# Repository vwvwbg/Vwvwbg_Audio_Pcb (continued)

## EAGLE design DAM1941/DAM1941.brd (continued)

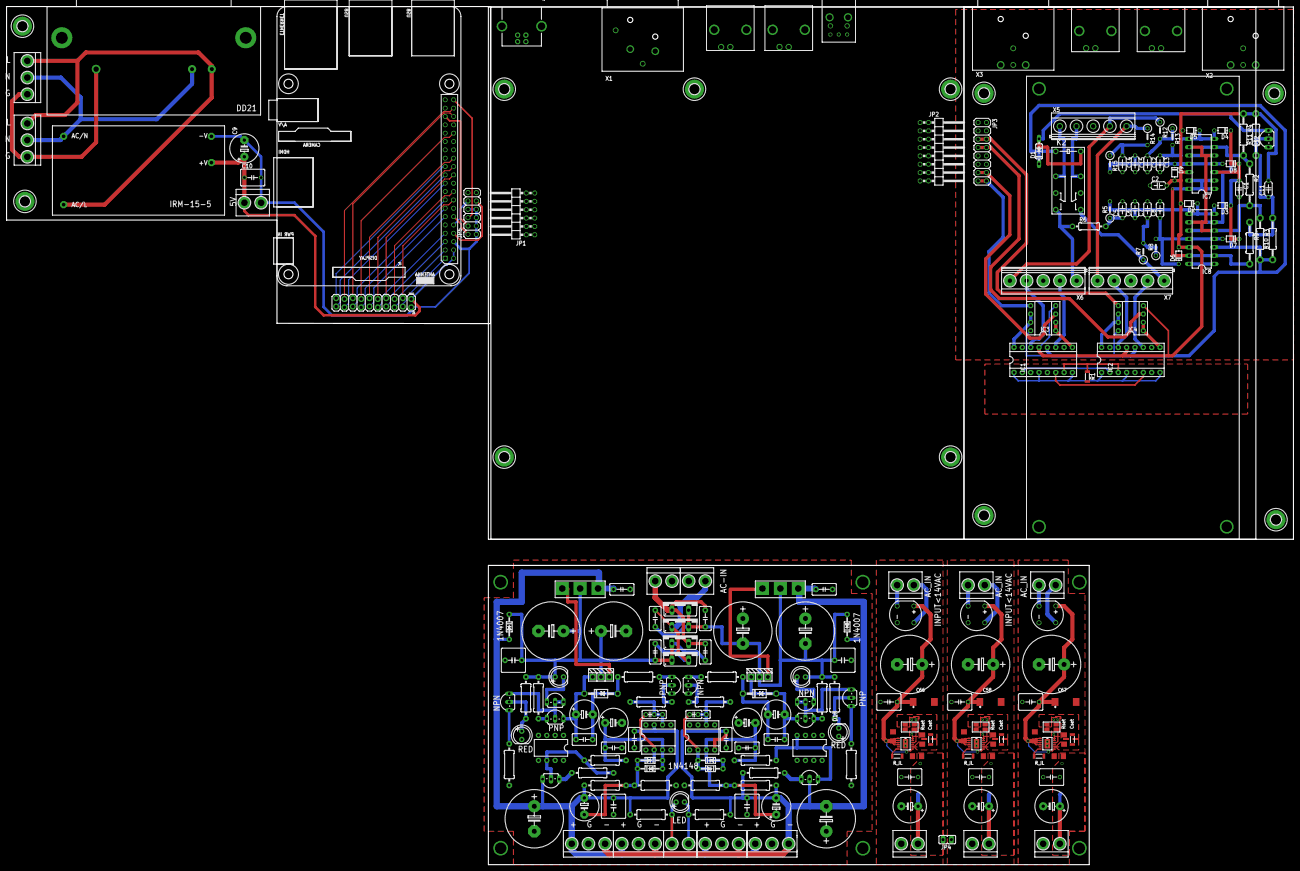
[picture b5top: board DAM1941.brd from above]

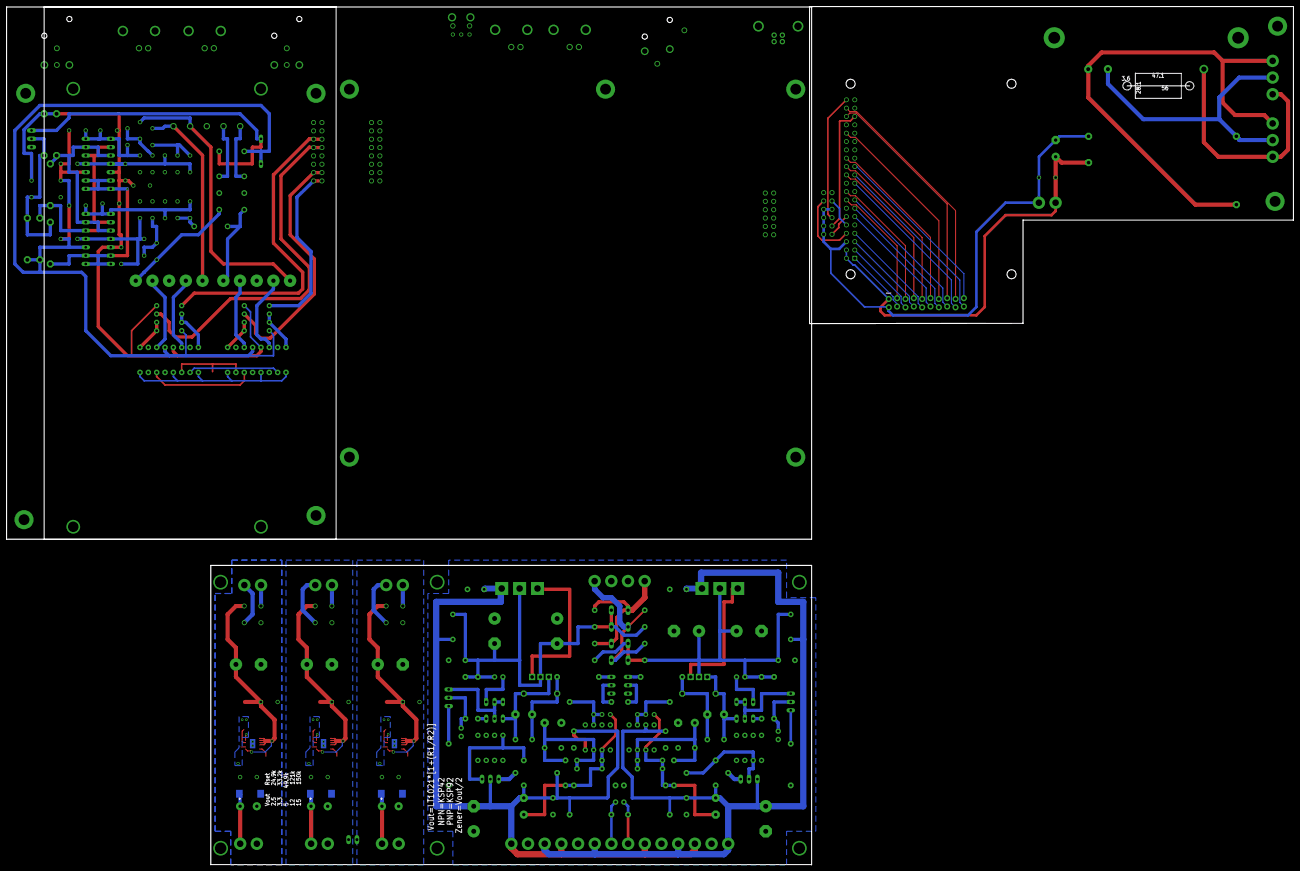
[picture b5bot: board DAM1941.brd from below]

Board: 2 copper layers, 391.8 x 261.2 mm, 221 parts (4 on the bottom side), 133 nets.

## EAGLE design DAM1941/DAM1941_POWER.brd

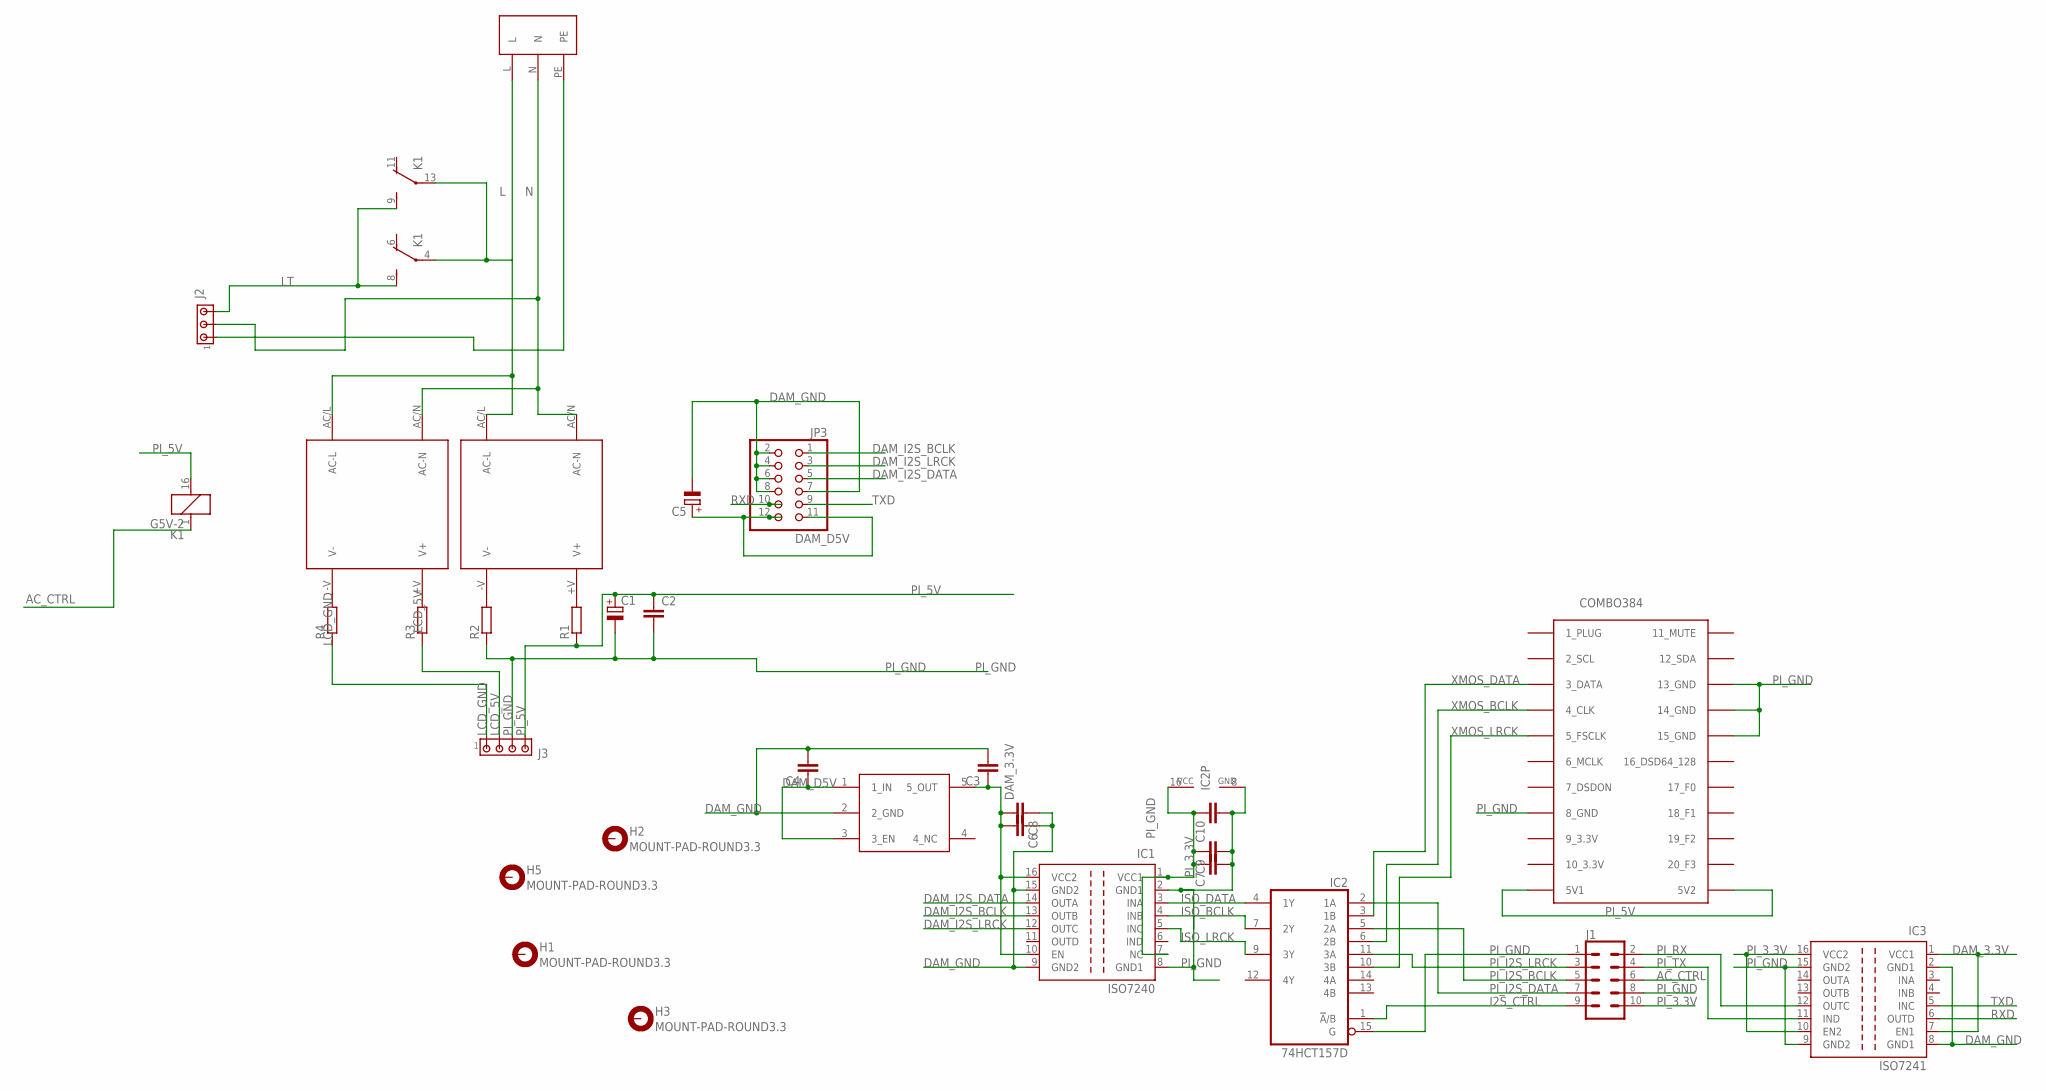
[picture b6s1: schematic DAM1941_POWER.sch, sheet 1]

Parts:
C1: CPOL-EUE5-8.5; E5-8,5
C2: C-EU050-050X075; C050-050X075
C3, C4, C6, C7, C8, C9, C10: C-EUC0805; C0805
C5: CPOL-EUSP-CAP-CX; SP-CAP-CX
H1, H2, H3, H5: MOUNT-PAD-ROUND3.3; 3,3-PAD
IC1: ISO7240; SO-16DW
IC2: 74HCT157D; SO16
IC3: ISO7241; SO-16DW
J1: CONN_05X2SHD_LOCK; 2X5-SHROUDED_LOCK
J2: MTA03-156; 1X3MTA
J3: MTA04-156; 1X4MTA
JP3: PINHD-2X6; 2X06
K1: G5V-2
R1, R2, R3, R4: R-EU_M1206; M1206
U$1: IRM-15-5; IRM-15
U$2: LP5907; SOT-23-5
U$3: IRM-10
U$4: COMBO384+8675
U$6: DD21; DD21.NOCOVER

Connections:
AC_CTRL: J1.6, K1.1
DAM_3.3V: C3.1, C6.2, C8.2, IC1.10 (EN), IC1.16 (VCC2), IC3.1 (VCC1), IC3.7 (EN1), U$2.5 (5_OUT)
DAM_D5V: C4.1, C5.+, JP3.11, JP3.12, U$2.1 (1_IN), U$2.3 (3_EN)
DAM_GND: C3.2, C4.2, C5.-, C6.1, C8.1, IC1.9 (GND2), IC1.15 (GND2), IC3.2 (GND1), IC3.8 (GND1), JP3.2, JP3.4, JP3.6, JP3.7, JP3.8, U$2.2 (2_GND)
DAM_I2S_BCLK: IC1.13 (OUTB), JP3.1
DAM_I2S_DATA: IC1.14 (OUTA), JP3.5
DAM_I2S_LRCK: IC1.12 (OUTC), JP3.3
I2S_CTRL: IC2.1 (!A!/B), J1.9
ISO_BCLK: IC1.4 (INB), IC2.7 (2Y)
ISO_DATA: IC1.3 (INA), IC2.4 (1Y)
ISO_LRCK: IC1.5 (INC), IC2.9 (3Y)
L: K1.4, K1.13, U$1.AC/L (AC-L), U$3.AC/L (AC-L), U$6.L
LCD_5V: J3.2, R3.1
LCD_GND: J3.1, R4.1
LT: J2.3, K1.8 (S), K1.9 (S)
N: J2.2, U$1.AC/N (AC-N), U$3.AC/N (AC-N), U$6.N
unnamed: R1.2, U$1.+V (V+)
unnamed: J2.1, U$6.PE
unnamed: R2.2, U$1.-V (V-)
unnamed: R3.2, U$3.+V (V+)
unnamed: R4.2, U$3.-V (V-)
PI_3.3V: C7.1, C9.1, C10.1, IC1.1 (VCC1), IC1.7 (NC), IC2.16 (VCC), IC3.10 (EN2), IC3.16 (VCC2), J1.10
PI_5V: C1.+, C2.1, J3.4, K1.16 (2), R1.1, U$4.5V1, U$4.5V2
PI_GND: C1.-, C2.2, C7.2, C9.2, C10.2, IC1.2 (GND1), IC1.8 (GND1), IC2.8 (GND), IC2.15 (G), IC3.9 (GND2), IC3.15 (GND2), J1.1, J1.8, J3.3, R2.1, U$4.8_GND, U$4.13_GND, U$4.14_GND, U$4.15_GND
PI_I2S_BCLK: IC2.5 (2A), J1.5
PI_I2S_DATA: IC2.2 (1A), J1.7
PI_I2S_LRCK: IC2.11 (3A), J1.3
PI_RX: IC3.12 (OUTC), J1.2
PI_TX: IC3.11 (IND), J1.4
RXD: IC3.6 (OUTD), JP3.10
TXD: IC3.5 (INC), JP3.9
XMOS_BCLK: IC2.6 (2B), U$4.4_CLD/DSDCLK (4_CLK)
XMOS_DATA: IC2.3 (1B), U$4.3_DATA/DSD1 (3_DATA)
XMOS_LRCK: IC2.10 (3B), U$4.5_FSCLK/DSD2 (5_FSCLK)

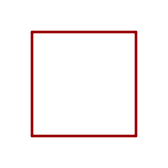
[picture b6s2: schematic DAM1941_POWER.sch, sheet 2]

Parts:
PCB2: RPI3-HOLE

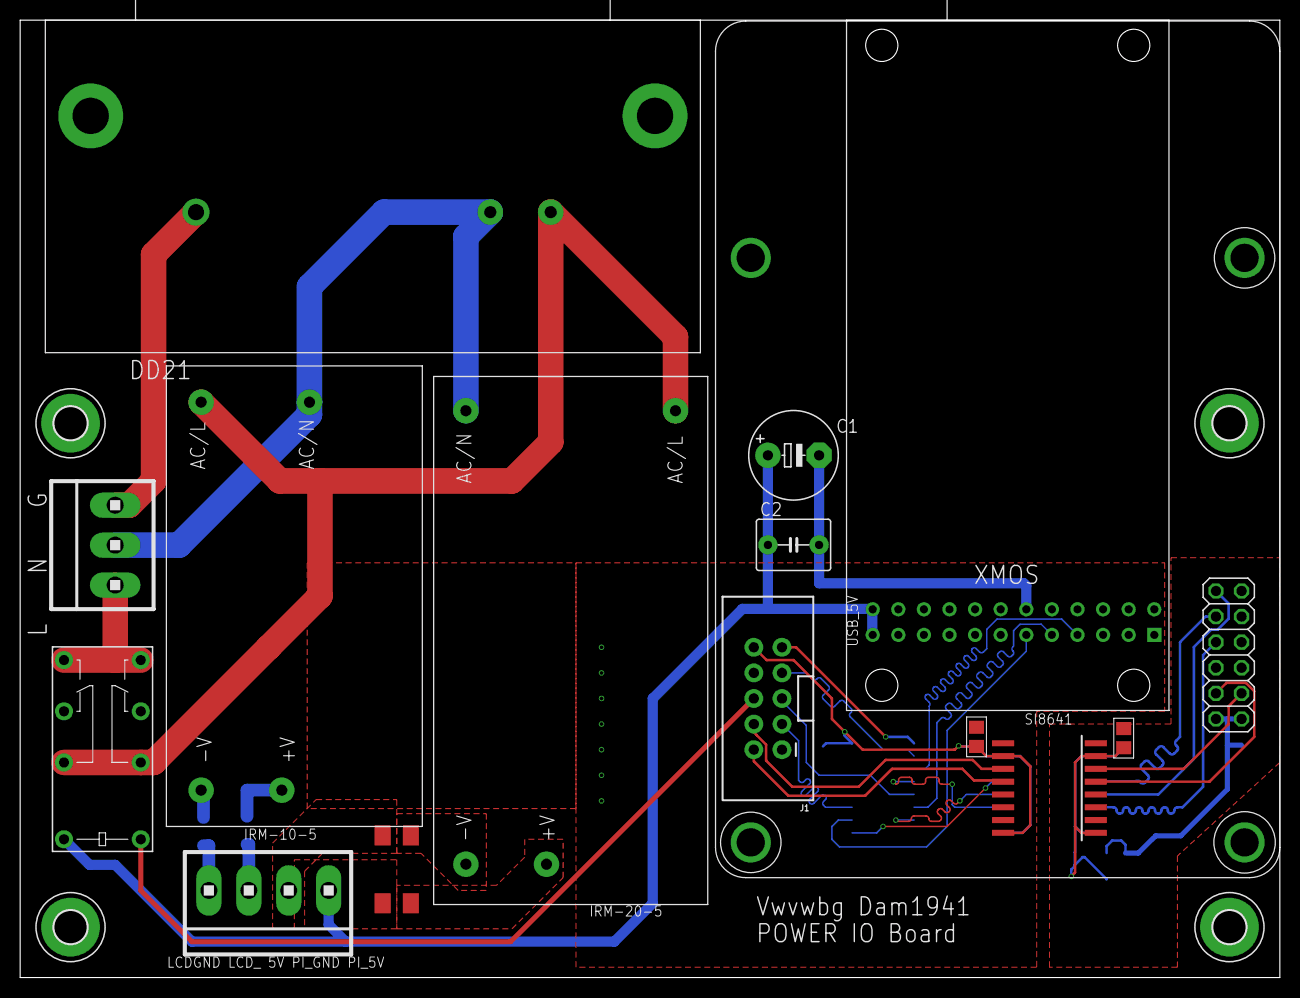
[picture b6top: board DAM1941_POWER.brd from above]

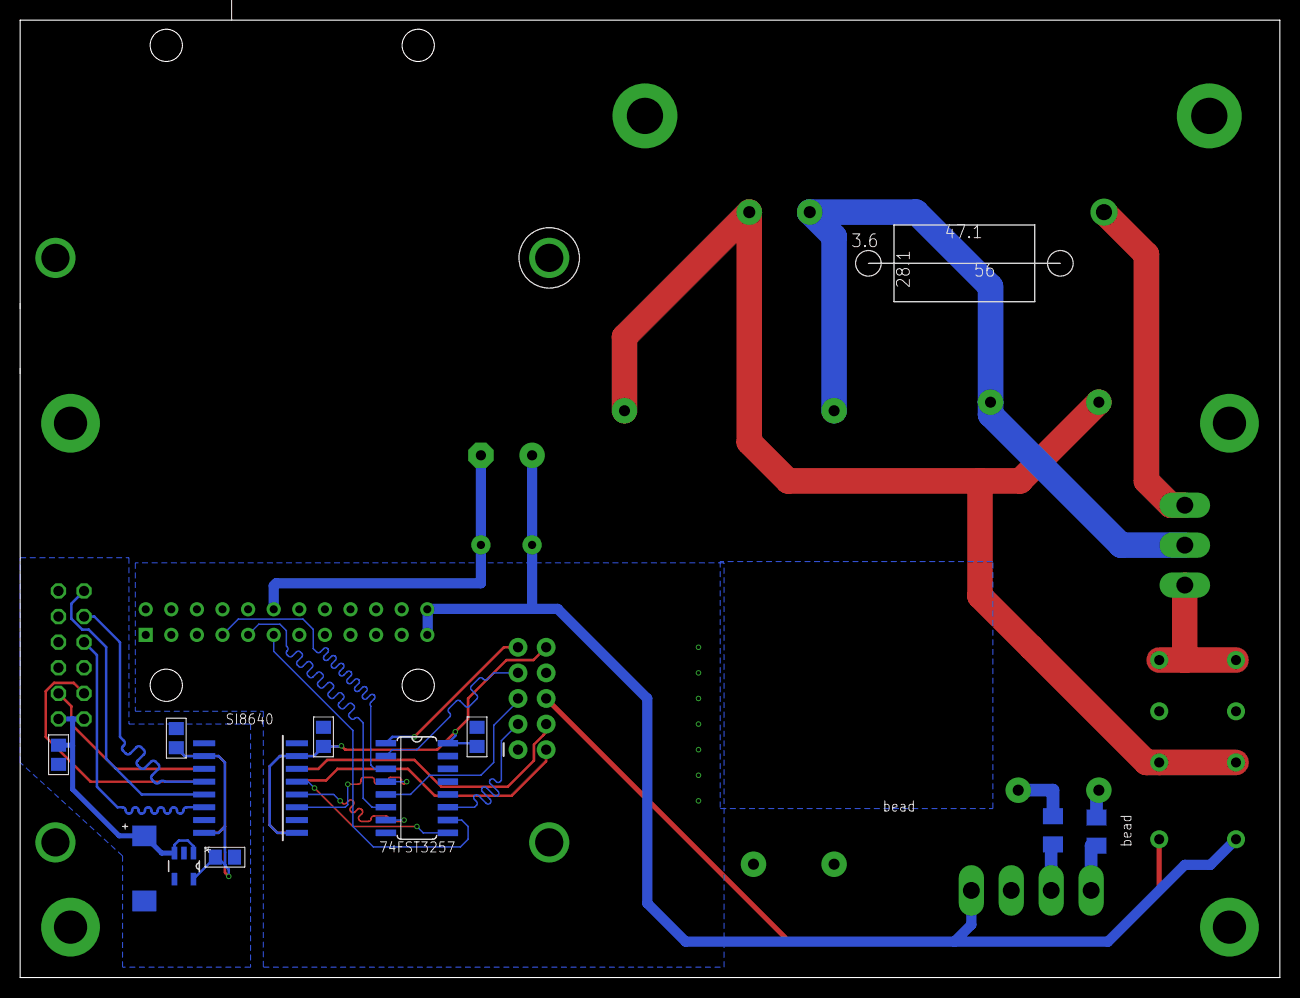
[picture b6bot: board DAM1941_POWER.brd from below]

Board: 2 copper layers, 125.0 x 95.0 mm, 32 parts (12 on the bottom side), 34 nets.

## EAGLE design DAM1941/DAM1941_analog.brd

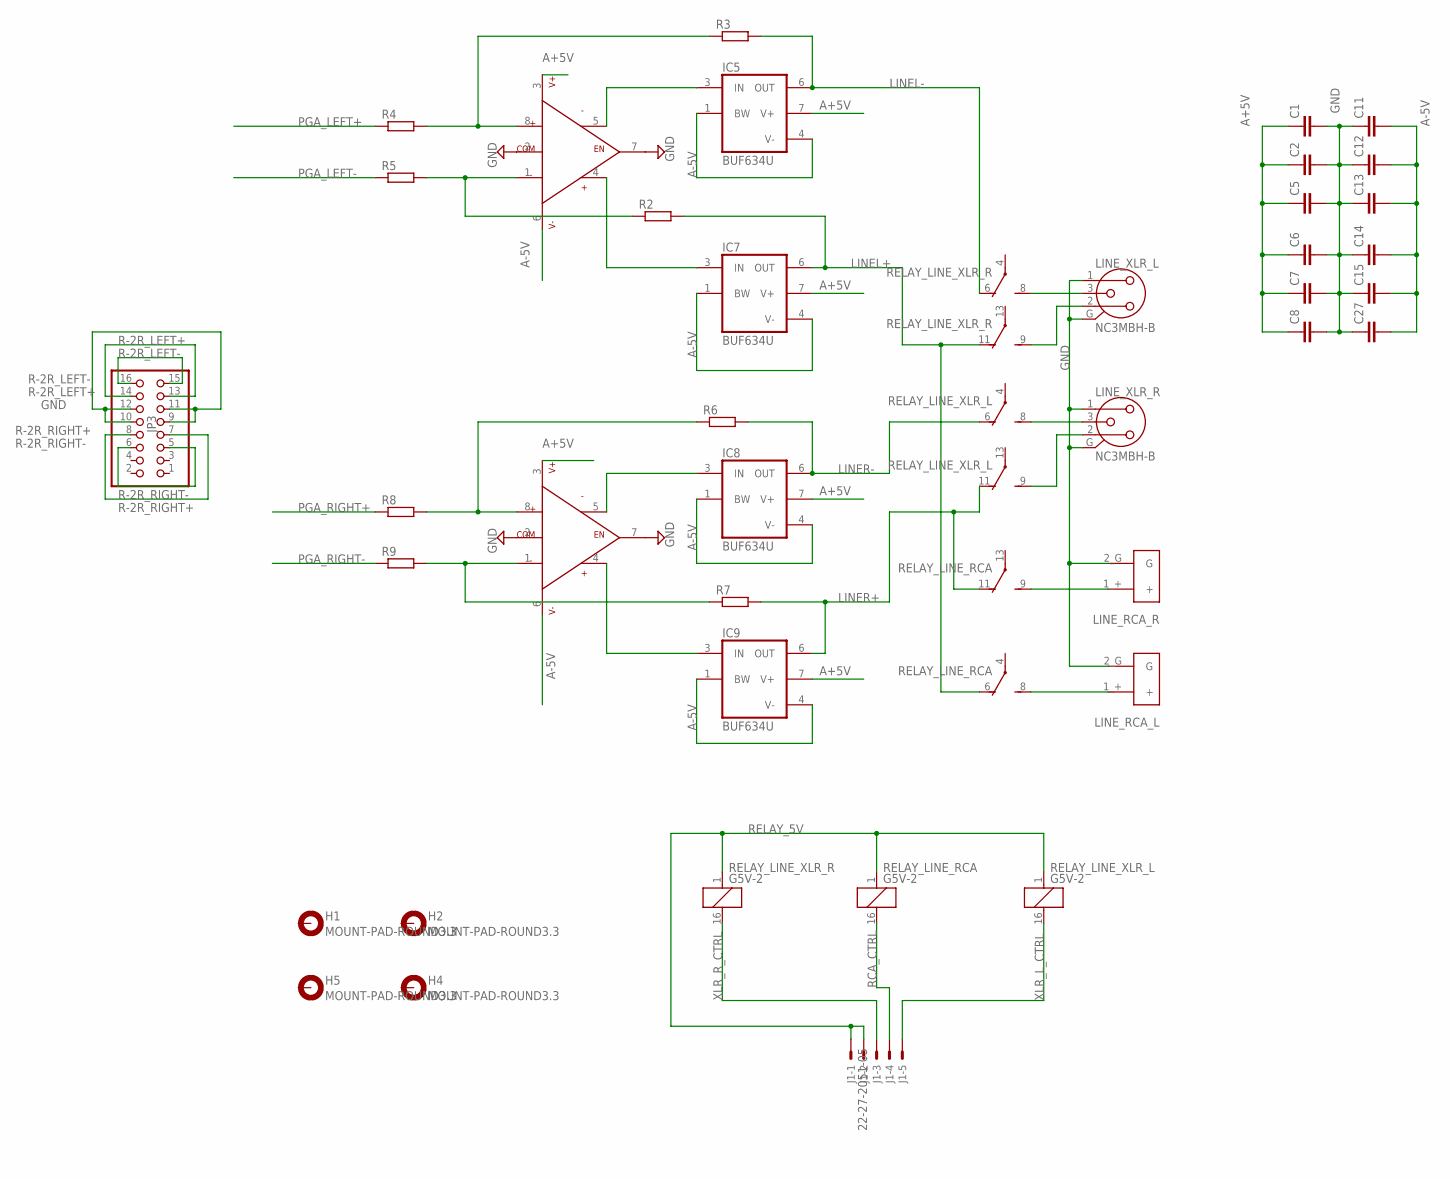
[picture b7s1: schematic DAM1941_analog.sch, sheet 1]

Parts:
C1, C2, C5, C6, C7, C8, C11, C12, C13, C14, C15, C27: C-EU050-050X075; C050-050X075
H1, H2, H4, H5: MOUNT-PAD-ROUND3.3; 3,3-PAD
IC5, IC7, IC8, IC9: BUF634U; SO08
J1: 22-27-2051-05; 6410-05
JP3: PINHD-2X8; 2X08
LINE_RCA_L: RCA
LINE_RCA_R: RCA
LINE_XLR_L: NC3MBH-B
LINE_XLR_R: NC3MBH-B
R2, R3, R4, R5, R6, R7, R8, R9: R-EU_0207/10; 0207/10
RELAY_LINE_RCA: G5V-2
RELAY_LINE_XLR_L: G5V-2
RELAY_LINE_XLR_R: G5V-2
U$1, U$2: OPA1632; SO8

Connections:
A+5V: C1.1, C2.1, C5.1, C6.1, C7.1, C8.1, IC5.7 (V+), IC7.7 (V+), IC8.7 (V+), IC9.7 (V+), U$1.3 (V+), U$2.3 (V+); also elsewhere on the board
A-5V: C11.2, C12.2, C13.2, C14.2, C15.2, C27.2, IC5.1 (BW), IC5.4 (V-), IC7.1 (BW), IC7.4 (V-), IC8.1 (BW), IC8.4 (V-), IC9.1 (BW), IC9.4 (V-), U$1.6 (V-), U$2.6 (V-); also elsewhere on the board
GND: C1.2, C2.2, C5.2, C6.2, C7.2, C8.2, C11.1, C12.1, C13.1, C14.1, C15.1, C27.1, JP3.9, JP3.10, JP3.11, JP3.12, LINE_RCA_L.2_G (G), LINE_RCA_R.2_G (G), LINE_XLR_L.1, LINE_XLR_L.G, LINE_XLR_R.1, LINE_XLR_R.G, U$1.2 (COM), U$1.7 (EN), U$2.2 (COM), U$2.7 (EN); also elsewhere on the board
LINEL+: IC7.6 (OUT), R2.2, RELAY_LINE_RCA.6 (O), RELAY_LINE_XLR_R.11 (O)
LINEL-: IC5.6 (OUT), R3.2, RELAY_LINE_XLR_R.6 (O)
LINER+: IC9.6 (OUT), R7.2, RELAY_LINE_RCA.11 (O), RELAY_LINE_XLR_L.11 (O)
LINER-: IC8.6 (OUT), R6.2, RELAY_LINE_XLR_L.6 (O)
unnamed: LINE_XLR_L.3, RELAY_LINE_XLR_R.8 (S)
unnamed: LINE_XLR_L.2, RELAY_LINE_XLR_R.9 (S)
unnamed: LINE_XLR_R.3, RELAY_LINE_XLR_L.8 (S)
unnamed: LINE_XLR_R.2, RELAY_LINE_XLR_L.9 (S)
unnamed: LINE_RCA_L.1_+ (+), RELAY_LINE_RCA.8 (S)
unnamed: LINE_RCA_R.1_+ (+), RELAY_LINE_RCA.9 (S)
unnamed: IC5.3 (IN), U$1.5 (OUT-)
unnamed: IC7.3 (IN), U$1.4 (OUT+)
unnamed: R3.1, R4.2, U$1.8 (IN+)
unnamed: R2.1, R5.2, U$1.1 (IN-)
unnamed: IC9.3 (IN), U$2.4 (OUT+)
unnamed: IC8.3 (IN), U$2.5 (OUT-)
unnamed: R6.1, R8.2, U$2.8 (IN+)
unnamed: R7.1, R9.2, U$2.1 (IN-)
PGA_LEFT+: R4.1; also elsewhere on the board
PGA_LEFT-: R5.1; also elsewhere on the board
PGA_RIGHT+: R8.1; also elsewhere on the board
PGA_RIGHT-: R9.1; also elsewhere on the board
R-2R_LEFT+: JP3.13, JP3.14; also elsewhere on the board
R-2R_LEFT-: JP3.15, JP3.16; also elsewhere on the board
R-2R_RIGHT+: JP3.7, JP3.8; also elsewhere on the board
R-2R_RIGHT-: JP3.5, JP3.6; also elsewhere on the board
RCA_CTRL: J1.4, RELAY_LINE_RCA.16 (2)
RELAY_5V: J1.1, J1.2, RELAY_LINE_RCA.1, RELAY_LINE_XLR_L.1, RELAY_LINE_XLR_R.1
XLR_L_CTRL: J1.5, RELAY_LINE_XLR_L.16 (2)
XLR_R_CTRL: J1.3, RELAY_LINE_XLR_R.16 (2)

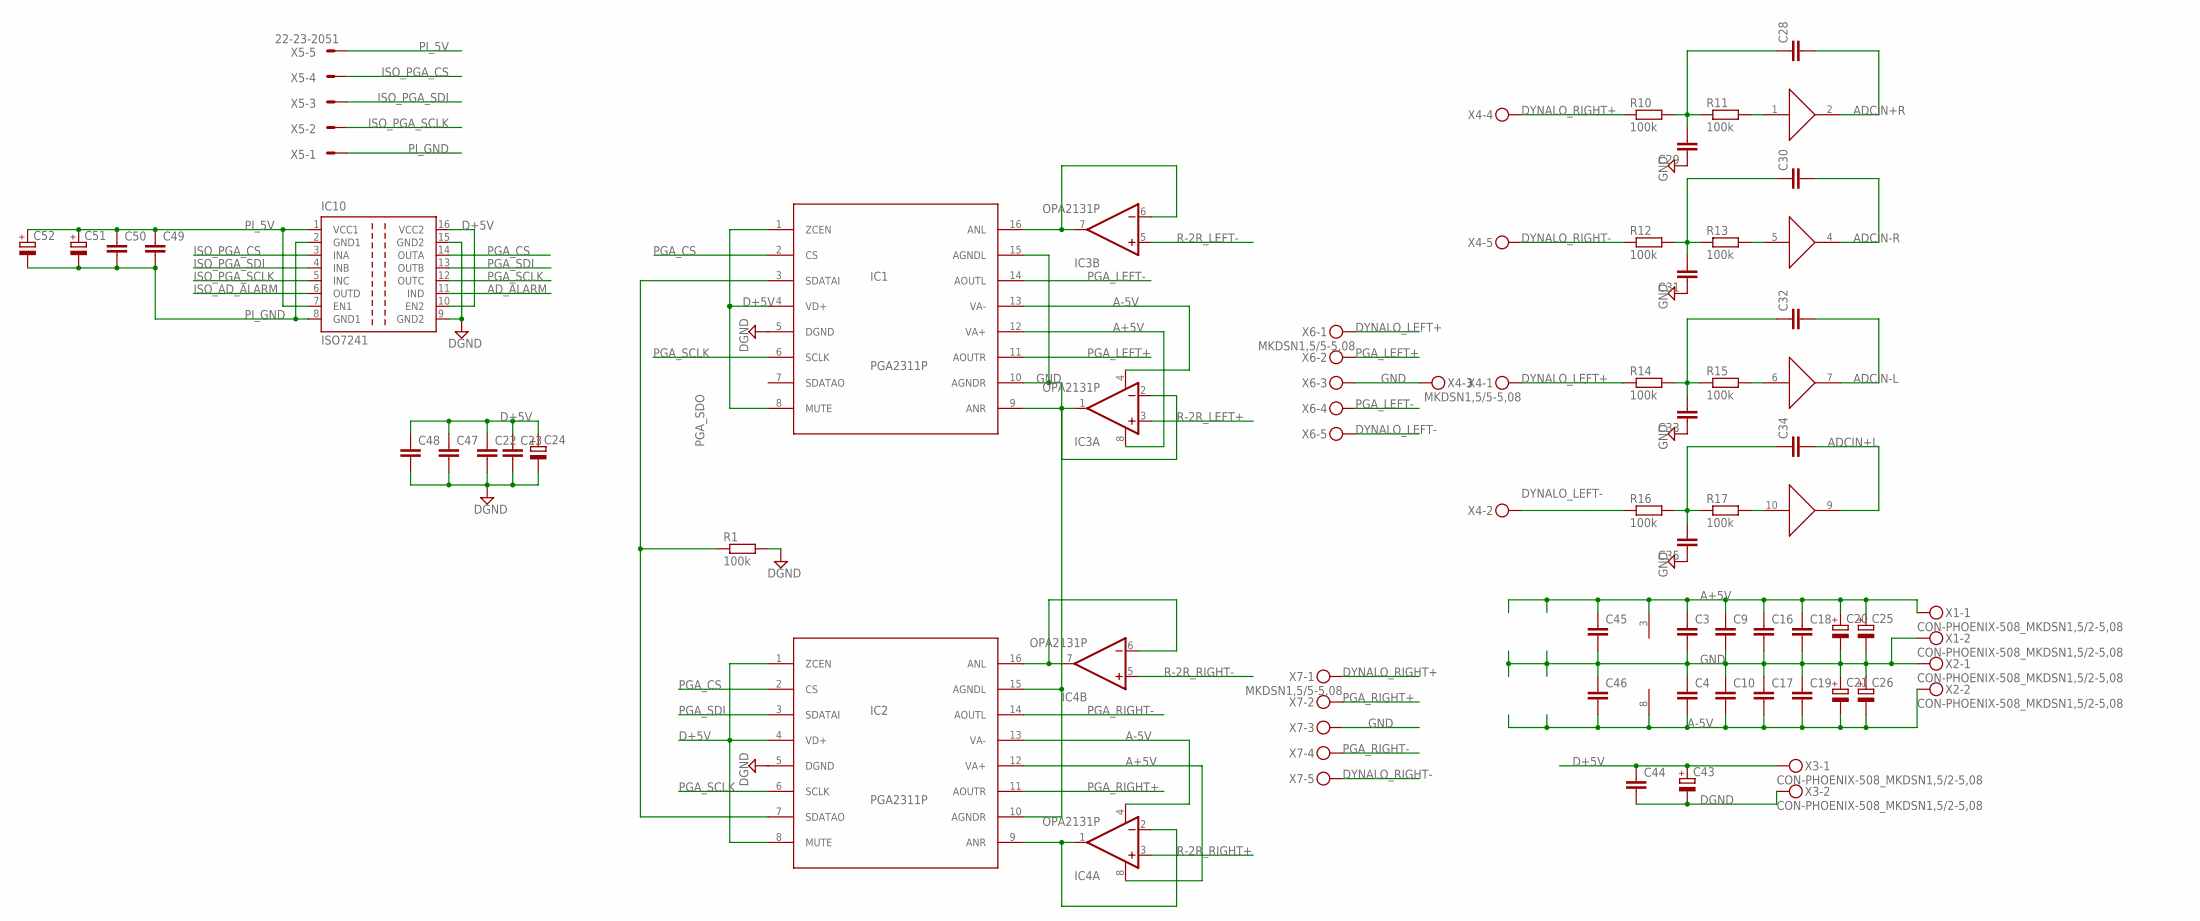
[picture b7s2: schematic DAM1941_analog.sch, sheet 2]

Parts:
C3, C4, C9, C10, C16, C17, C18, C19, C22, C23, C44: C-EU050-050X075; C050-050X075
C20, C21, C24, C43: CPOL-EUE5-10.5; E5-10,5
C25, C26: CPOL-EUE5-13; E5-13
C28, C29, C30, C31, C32, C33, C34, C35: C-EUC1206; C1206
C45, C46, C47, C48, C49, C50: C-EUC0603K; C0603K
C51, C52: CPOL-EUE5-8.5; E5-8,5
IC1, IC2: PGA2311P; DIL16
IC3, IC4: OPA2131P; DIL08
IC10: ISO7241; SO-16DW
R1, R10, R11, R12, R13, R14, R15, R16, R17: 100k; MINI_MELF-0204R
U$3: AD8244; MSOP10
X1, X2, X3: CON-PHOENIX-508_MKDSN1,5/2-5,08
X4, X6, X7: MKDSN1,5/5-5,08
X5: 22-23-2051

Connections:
A+5V: C3.1, C9.1, C16.1, C18.1, C20.+, C25.+, C45.1, IC1.12 (VA+), IC2.12 (VA+), IC3.8 (V+), IC4.8 (V+), U$3.3 (V+), X1.1; also elsewhere on the board
A-5V: C4.2, C10.2, C17.2, C19.2, C21.-, C26.-, C46.2, IC1.13 (VA-), IC2.13 (VA-), IC3.4 (V-), IC4.4 (V-), U$3.8 (V-), X2.2; also elsewhere on the board
ADCIN+L: C34.2, U$3.9 (OUT); also elsewhere on the board
ADCIN+R: C28.2, U$3.2 (OUT); also elsewhere on the board
ADCIN-L: C32.2, U$3.7 (OUT); also elsewhere on the board
ADCIN-R: C30.2, U$3.4 (OUT); also elsewhere on the board
AD_ALARM: IC10.11 (IND); also elsewhere on the board
D+5V: C22.1, C23.1, C24.+, C43.+, C44.1, C47.1, C48.1, IC1.1 (ZCEN), IC1.4 (VD+), IC1.8 (MUTE), IC2.1 (ZCEN), IC2.4 (VD+), IC2.8 (MUTE), IC10.10 (EN2), IC10.16 (VCC2), X3.1; also elsewhere on the board
DGND: C22.2, C23.2, C24.-, C43.-, C44.2, C47.2, C48.2, IC1.5 (DGND), IC2.5 (DGND), IC10.9 (GND2), IC10.15 (GND2), R1.2, X3.2; also elsewhere on the board
DYNALO_LEFT+: R14.1, X4.1, X6.1
DYNALO_LEFT-: R16.1, X4.2, X6.5
DYNALO_RIGHT+: R10.1, X4.4, X7.1
DYNALO_RIGHT-: R12.1, X4.5, X7.5
GND: C3.2, C4.1, C9.2, C10.1, C16.2, C17.1, C18.2, C19.1, C20.-, C21.+, C25.-, C26.+, C29.1, C31.1, C33.1, C35.1, C45.2, C46.1, IC1.10 (AGNDR), IC1.15 (AGNDL), IC2.10 (AGNDR), IC2.15 (AGNDL), X1.2, X2.1, X4.3, X6.3, X7.3; also elsewhere on the board
ISO_AD_ALARM: IC10.6 (OUTD); also elsewhere on the board
ISO_PGA_CS: IC10.3 (INA), X5.4
ISO_PGA_SCLK: IC10.5 (INC), X5.2
ISO_PGA_SDI: IC10.4 (INB), X5.3
unnamed: IC2.9 (ANR), IC4.1 (OUT), IC4.2 (-IN)
unnamed: IC2.16 (ANL), IC4.6 (-IN), IC4.7 (OUT)
unnamed: IC1.9 (ANR), IC3.1 (OUT), IC3.2 (-IN)
unnamed: IC1.16 (ANL), IC3.6 (-IN), IC3.7 (OUT)
unnamed: C28.1, C29.2, R10.2, R11.1
unnamed: R11.2, U$3.1 (IN)
unnamed: C30.1, C31.2, R12.2, R13.1
unnamed: R13.2, U$3.5 (IN)
unnamed: C32.1, C33.2, R14.2, R15.1
unnamed: R15.2, U$3.6 (IN)
unnamed: C34.1, C35.2, R16.2, R17.1
unnamed: R17.2, U$3.10 (IN)
PGA_CS: IC1.2 (CS), IC2.2 (CS), IC10.14 (OUTA)
PGA_LEFT+: IC1.11 (AOUTR), X6.2; also elsewhere on the board
PGA_LEFT-: IC1.14 (AOUTL), X6.4; also elsewhere on the board
PGA_RIGHT+: IC2.11 (AOUTR), X7.2; also elsewhere on the board
PGA_RIGHT-: IC2.14 (AOUTL), X7.4; also elsewhere on the board
PGA_SCLK: IC1.6 (SCLK), IC2.6 (SCLK), IC10.12 (OUTC)
PGA_SDI: IC2.3 (SDATAI), IC10.13 (OUTB)
PGA_SDO: IC1.3 (SDATAI), IC2.7 (SDATAO), R1.1
PI_5V: C49.1, C50.1, C51.+, C52.+, IC10.1 (VCC1), IC10.7 (EN1), X5.5; also elsewhere on the board
PI_GND: C49.2, C50.2, C51.-, C52.-, IC10.2 (GND1), IC10.8 (GND1), X5.1; also elsewhere on the board
R-2R_LEFT+: IC3.3 (+IN); also elsewhere on the board
R-2R_LEFT-: IC3.5 (+IN); also elsewhere on the board
R-2R_RIGHT+: IC4.3 (+IN); also elsewhere on the board
R-2R_RIGHT-: IC4.5 (+IN); also elsewhere on the board

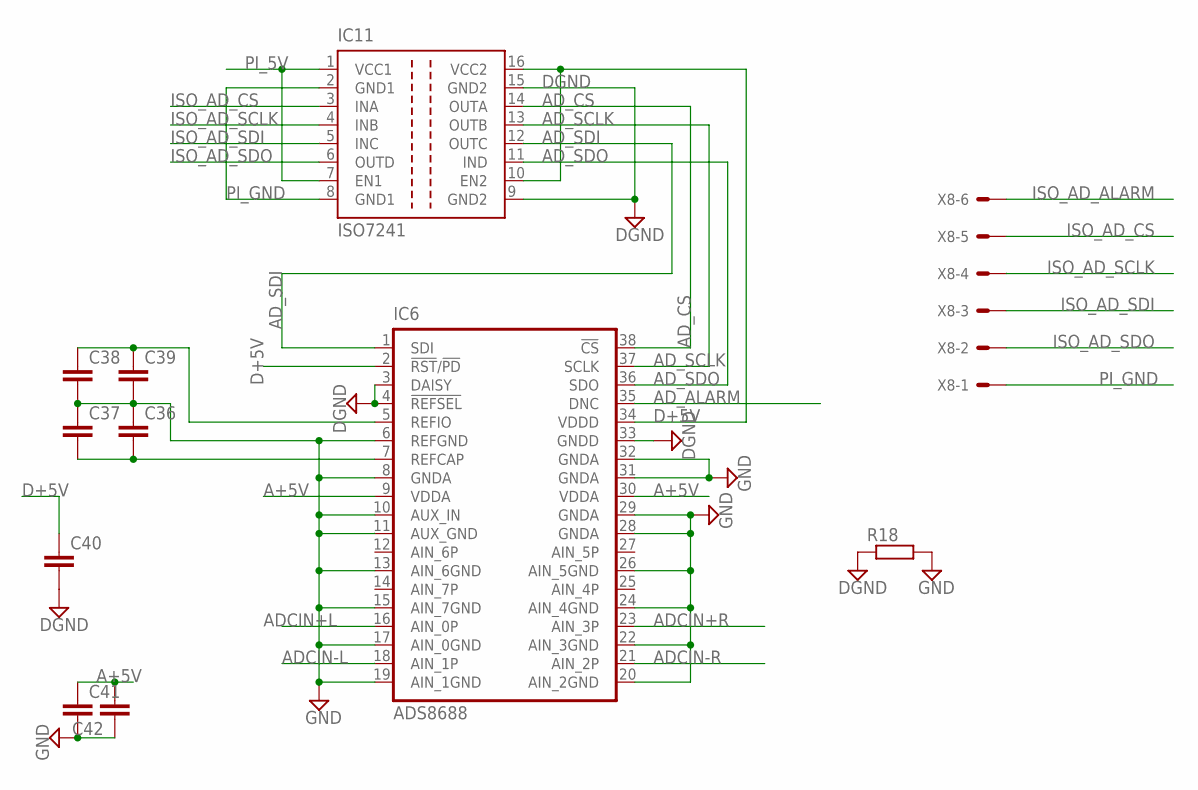
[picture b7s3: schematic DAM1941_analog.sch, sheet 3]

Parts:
C36, C39, C40, C41, C42: C-EUC0603K; C0603K
C37, C38: C-EU050-035X075; C050-035X075
IC6: ADS8688; DBT_R-PDSO-G38
IC11: ISO7241; SO-16DW
R18: R-EU_MELF0204R; MINI_MELF-0204R
X8: 22-23-2061

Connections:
A+5V: C41.1, C42.2, IC6.9 (VDDA), IC6.30 (VDDA); also elsewhere on the board
ADCIN+L: IC6.16 (AIN_0P); also elsewhere on the board
ADCIN+R: IC6.23 (AIN_3P); also elsewhere on the board
ADCIN-L: IC6.18 (AIN_1P); also elsewhere on the board
ADCIN-R: IC6.21 (AIN_2P); also elsewhere on the board
AD_ALARM: IC6.35 (DNC); also elsewhere on the board
AD_CS: IC6.38 (!CS), IC11.14 (OUTA)
AD_SCLK: IC6.37 (SCLK), IC11.13 (OUTB)
AD_SDI: IC6.1 (SDI), IC11.12 (OUTC)
AD_SDO: IC6.36 (SDO), IC11.11 (IND)
D+5V: C40.1, IC6.2 (!RST!/!PD), IC6.34 (VDDD), IC11.10 (EN2), IC11.16 (VCC2); also elsewhere on the board
DGND: C40.2, IC6.3 (DAISY), IC6.4 (!REFSEL), IC6.33 (GNDD), IC11.9 (GND2), IC11.15 (GND2), R18.1; also elsewhere on the board
GND: C36.1, C37.1, C38.2, C39.2, C41.2, C42.1, IC6.6 (REFGND), IC6.8 (GNDA), IC6.10 (AUX_IN), IC6.11 (AUX_GND), IC6.13 (AIN_6GND), IC6.15 (AIN_7GND), IC6.17 (AIN_0GND), IC6.19 (AIN_1GND), IC6.20 (AIN_2GND), IC6.22 (AIN_3GND), IC6.24 (AIN_4GND), IC6.26 (AIN_5GND), IC6.28 (GNDA), IC6.29 (GNDA), IC6.31 (GNDA), IC6.32 (GNDA), R18.2; also elsewhere on the board
ISO_AD_ALARM: X8.6; also elsewhere on the board
ISO_AD_CS: IC11.3 (INA), X8.5
ISO_AD_SCLK: IC11.4 (INB), X8.4
ISO_AD_SDI: IC11.5 (INC), X8.3
ISO_AD_SDO: IC11.6 (OUTD), X8.2
unnamed: C36.2, C37.2, IC6.7 (REFCAP)
unnamed: C38.1, C39.1, IC6.5 (REFIO)
PI_5V: IC11.1 (VCC1), IC11.7 (EN1); also elsewhere on the board
PI_GND: IC11.2 (GND1), IC11.8 (GND1), X8.1; also elsewhere on the board

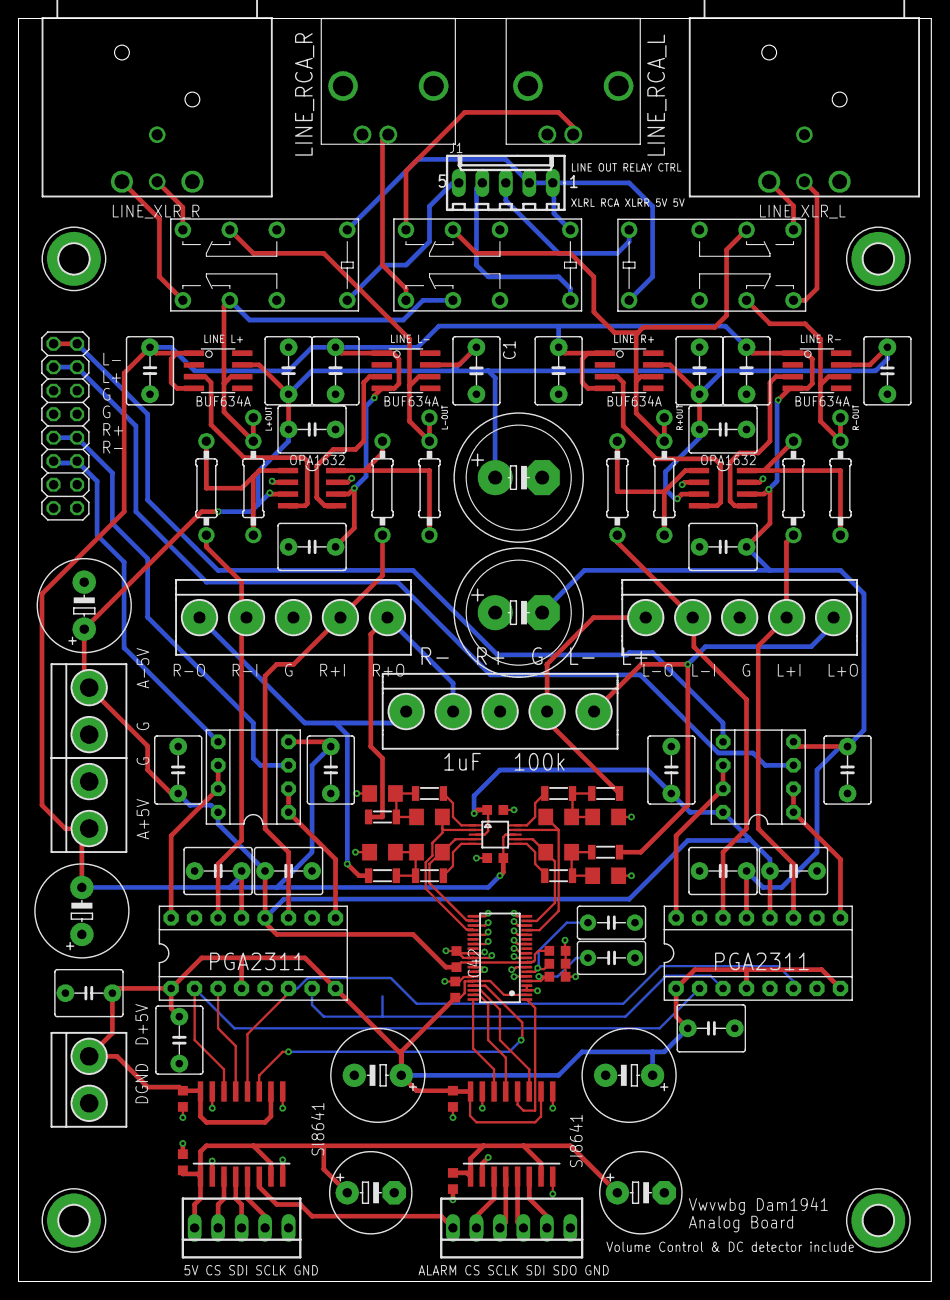
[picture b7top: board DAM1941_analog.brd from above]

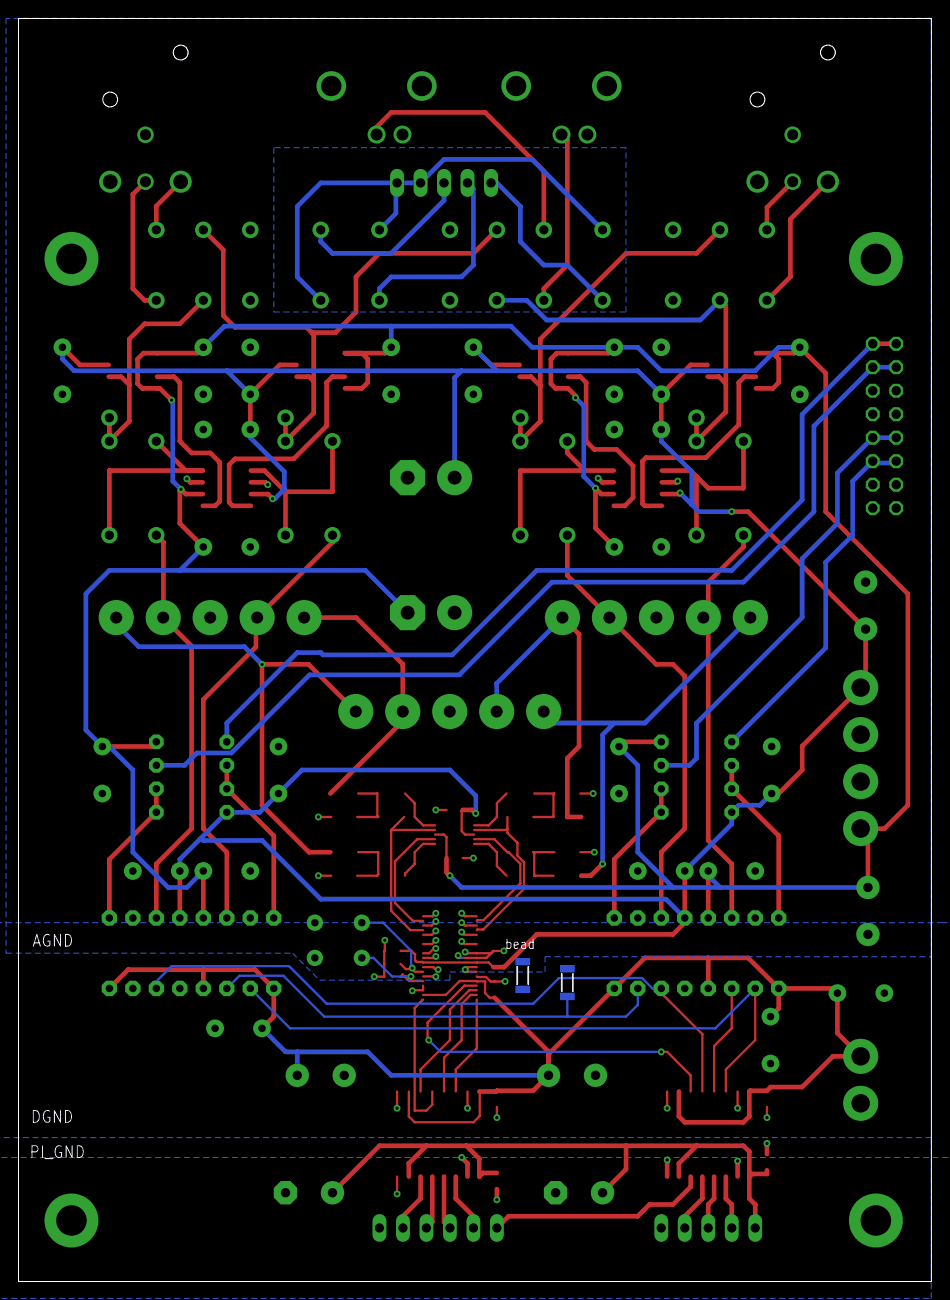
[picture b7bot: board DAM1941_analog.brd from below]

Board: 2 copper layers, 98.7 x 136.6 mm, 105 parts (2 on the bottom side), 76 nets.
